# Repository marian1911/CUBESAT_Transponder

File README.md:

Todos los archivos de diseño, simulaciones, componentes y codigo referido a transponder cubesat VHF-UHF

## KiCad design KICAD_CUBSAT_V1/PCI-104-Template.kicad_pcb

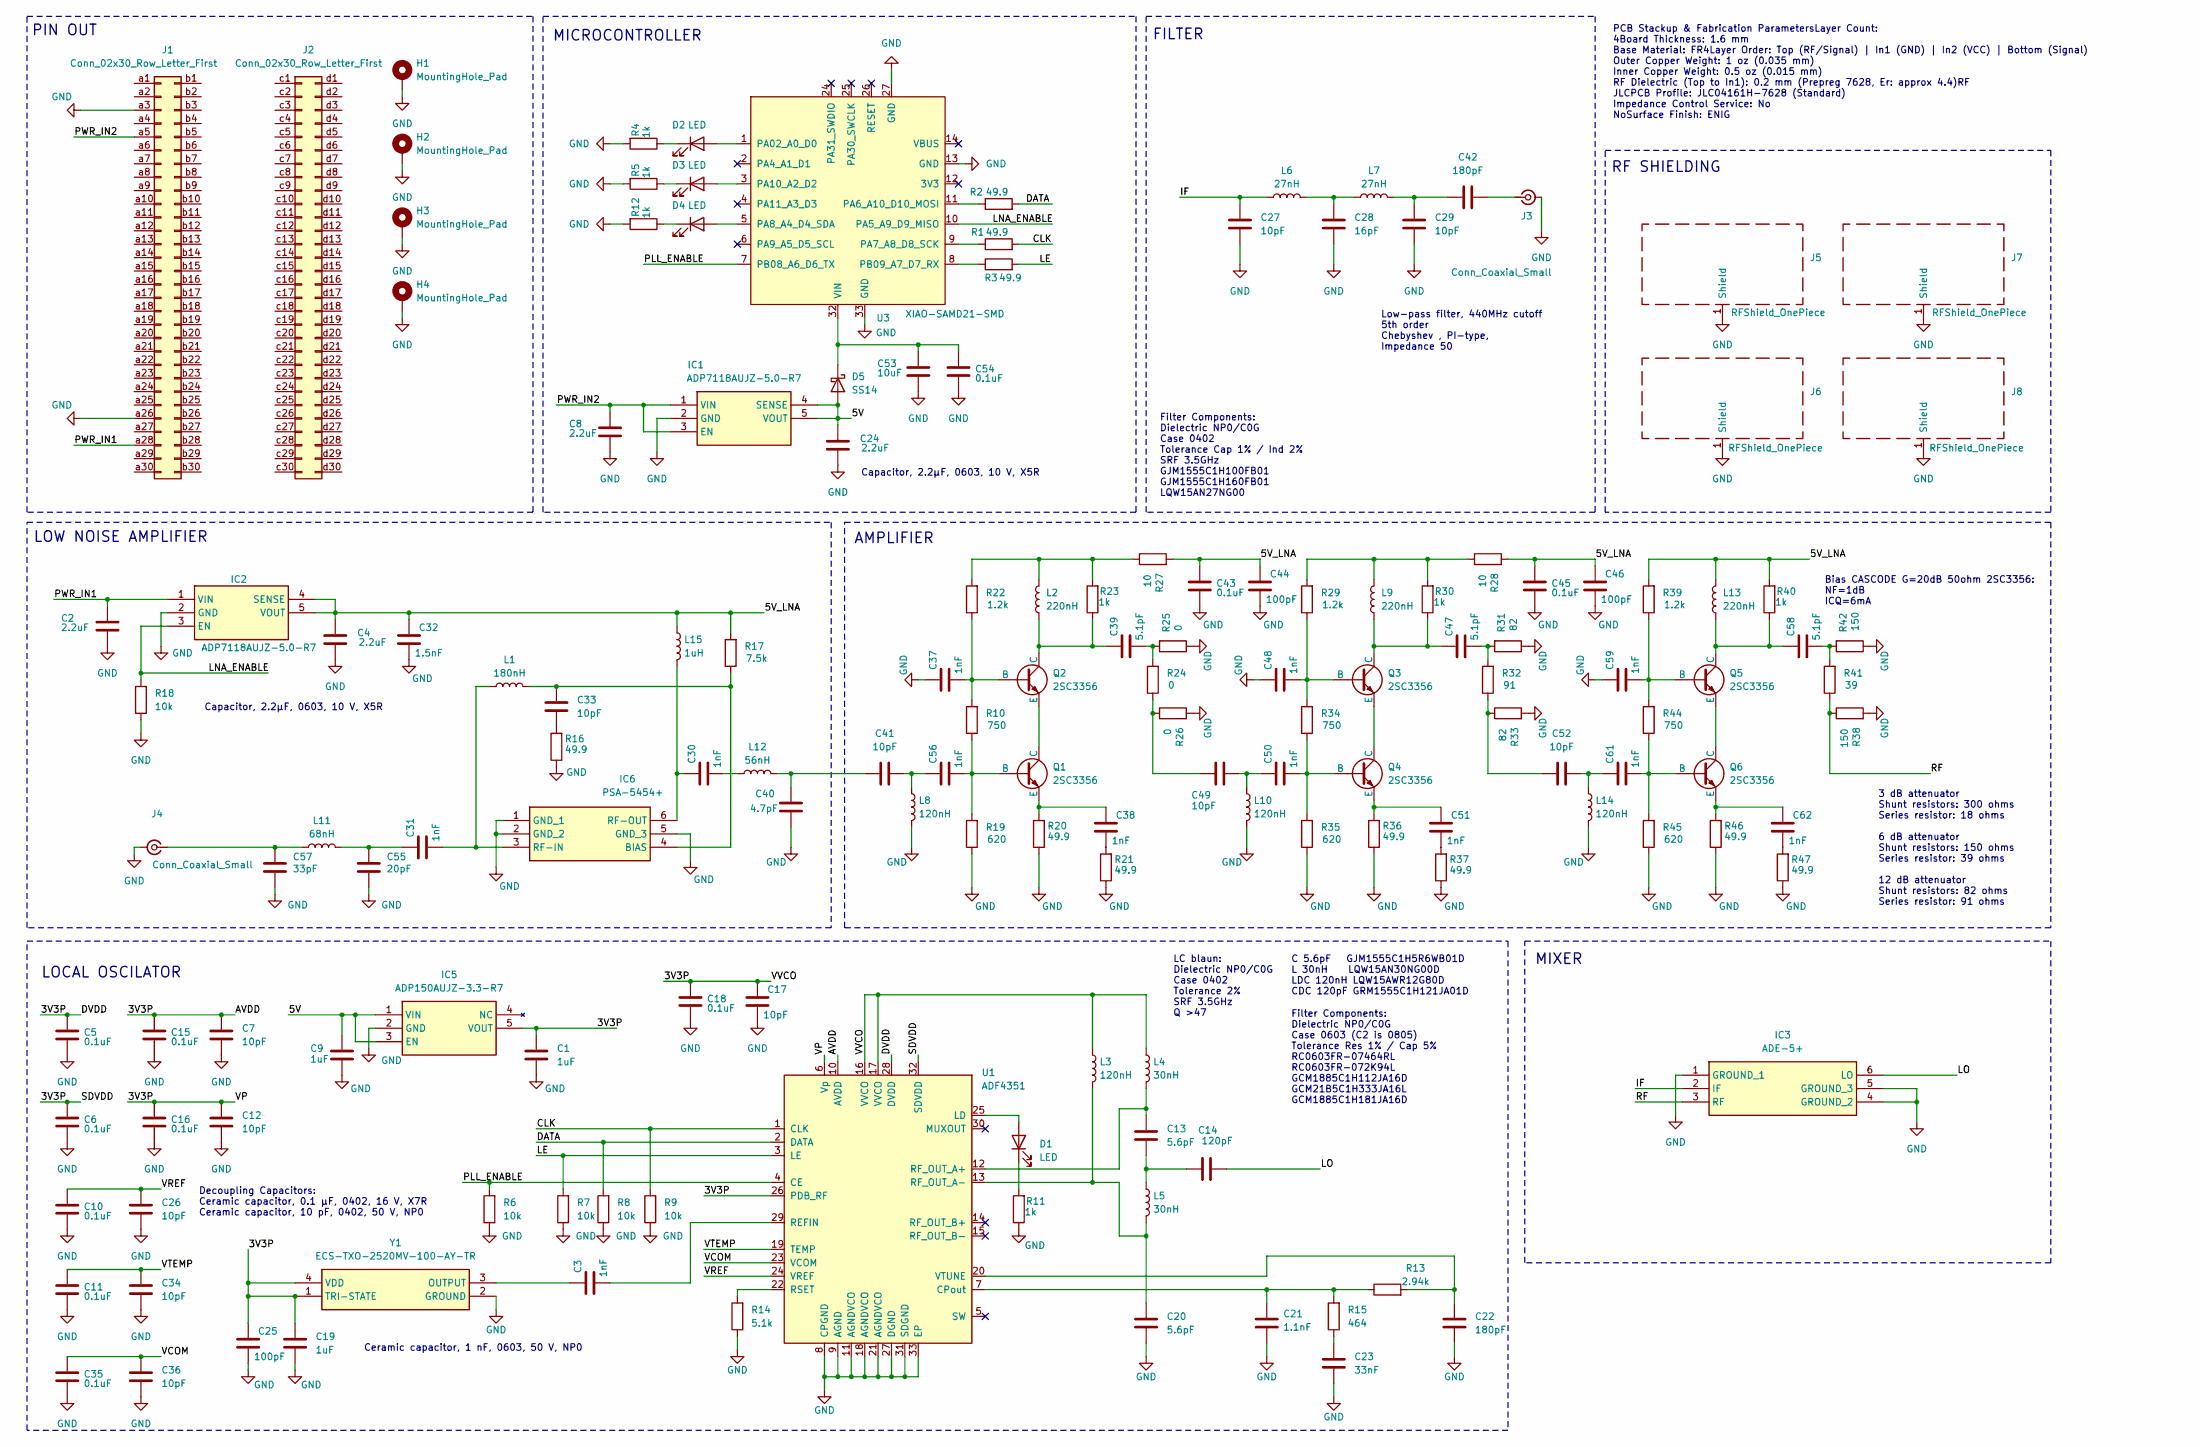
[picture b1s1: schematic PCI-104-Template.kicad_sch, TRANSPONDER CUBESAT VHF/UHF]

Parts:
C1, C9, C19: 1uF; C_0603_1608Metric; Mouser Part Number 81-GRM39R105K10
C2, C4, C8, C24: 2.2uF; C_0603_1608Metric; Mouser Part Number 81-GRM188R61E225KA2D
C3, C30, C31, C37, C38, C48, C50, C51, C56, C59, C61, C62: 1nF; C_0603_1608Metric; Manufacturer_Part_Number GRM1885C1H102JA01D; Mouser Part Number 81-GRM39C102J50
C5, C6, C10, C11, C15, C16, C18, C35, C43, C45, C54: 0.1uF; C_0402_1005Metric; Manufacturer_Part_Number GRM155R71C104KA88D; Mouser Part Number 81-GRM155R71C104KA88
C7, C12, C26, C27, C29, C33, C34, C36, C41, C49, C52: 10pF; C_0402_1005Metric; Manufacturer_Part_Number GJM1555C1H100FB01D; Mouser Part Number 81-GJM1555C1H100FB01
C13, C20: 5.6pF; C_0402_1005Metric; Manufacturer_Part_Number GJM1555C1H5R6WB01D; Mouser Part Number 81-GJM1555C1H5R6WB1D
C14: 120pF; C_0402_1005Metric; Mouser Part Number 81-GRM1555C1H121JA01
C17: 10pF; C_0402_1005Metric; Manufacturer_Part_Number GRM1555C1H100JA01D; Mouser Part Number 81-GRM1555C1H100JA1D
C21: 1.1nF; C_0603_1608Metric; Mouser Part Number 81-GCM1885C1H112JA6D
C22, C42: 180pF; C_0603_1608Metric; Mouser Part Number 81-GCM1885C1H181J16D
C23: 33nF; C_0805_2012Metric; Mouser Part Number 81-GCM21B5C2A333GE2L
C25, C44, C46: 100pF; C_0402_1005Metric; Manufacturer_Part_Number GCM1555C1H101FA16J; Mouser Part Number 81-GCM1555C1H101FA6J
C28: 16pF; C_0402_1005Metric; Manufacturer_Part_Number GJM1555C1H160FB01J; Mouser Part Number 81-GJM1555C1H160FB1J
C32: 1.5nF; C_0603_1608Metric; Manufacturer_Part_Number GRM1885C1H152JA01J; Mouser Part Number 81-GRM185C1H152JA01J
C39, C47, C58: 5.1pF; C_0402_1005Metric; Manufacturer_Part_Number GJM0225C1C5R1BB01L; Mouser Part Number 81-GJM0225C1C5R1BB1L
C40: 4.7pF; C_0402_1005Metric; Manufacturer_Part_Number GJM0225C1E4R7BB01L; Mouser Part Number 81-GJM0225C1E4R7BB1L
C53: 10uF; C_0805_2012Metric; Mouser Part Number 81-GRT21BR61E106KE3L
C55: 20pF; C_0402_1005Metric; Manufacturer_Part_Number GJM1555C1H200FB01D; Mouser Part Number 81-GJM1555C1H200FB1D
C57: 33pF; C_0402_1005Metric; Manufacturer_Part_Number GCM1555C1H330FA16J; Mouser Part Number 81-GCM1555C1H330FA6J
D1, D2, D3, D4: LED; LED_0603_1608Metric; Manufacturer_Part_Number LTST-C190GKT; Mouser Part Number 859-LTST-C190GKT
D5: SS14; D_SMA; Mouser Part Number 512-SS14
H1, H2, H3, H4: MountingHole_Pad; MountingHole_3.2mm_M3_Pad_TopBottom
IC1, IC2: ADP7118AUJZ-5.0-R7; SOT95P280X100-5N; Mouser Part Number 584-P7118WAUJZ-50-R
IC3: ADE-5+; ADE5; Mouser Part Number 139-ADE-5
IC5: ADP150AUJZ-3.3-R7; SOT95P280X100-5N; Mouser Part Number 584-ADP150AUJZ3.3R7
IC6: PSA-5454+; SOT65P215X100-6N; Mouser Part Number 139-PSA-5454
J1, J2: Conn_02x30_Row_Letter_First; PinSocket_2x30_P2.00mm_Vertical
J3, J4: Conn_Coaxial_Small; SMA_Samtec_SMA-J-P-H-ST-EM1_EdgeMount; Manufacturer_Part_Number SMA-J-P-H-ST-EM1; Mouser Part Number 200-SMAJPHSTEM1
J5, J6, J7, J8: RFShield_OnePiece; Laird_Technologies_BMI-S-102_16.50x16.50mm; Manufacturer_Part_Number BMI-S-102; Mouser Part Number 739-BMI-S-102
L1: 180nH; L_0402_1005Metric; Manufacturer_Part_Number LQW15AWR18J80D; Mouser Part Number 81-LQW15AWR18J80D
L2, L9, L13: 220nH; L_0402_1005Metric; Manufacturer_Part_Number LQW18ANR22G00D; Mouser Part Number 81-LQW18ANR22G00D
L3, L8, L10, L14: 120nH; L_0402_1005Metric; Manufacturer_Part_Number LQW15AWR12G80D; Mouser Part Number 81-LQW15AWR12G80D
L4, L5: 30nH; L_0402_1005Metric; Manufacturer_Part_Number LQW15AN30NG00D; Mouser Part Number 81-LQW15AN30NG00D
L6, L7: 27nH; L_0402_1005Metric; Manufacturer_Part_Number LQW15AN27NG00D; Mouser Part Number 81-LQW15AN27NG00D
L11: 68nH; L_0402_1005Metric; Manufacturer_Part_Number LQW15AN68NG0ZD; Mouser Part Number 81-LQW15AN68NG0ZD
L12: 56nH; L_0402_1005Metric; Manufacturer_Part_Number LQW15AN56NG8ZD; Mouser Part Number 81-LQW15AN56NG8ZD
L15: 1uH; L_0805_2012Metric; Manufacturer_Part_Number LQW21FT1R0M0HL; Mouser Part Number 81-LQW21FT1R0M0HL
Q1, Q2, Q3, Q4, Q5, Q6: 2SC3356; SOT-23
R1, R2, R3, R16, R20, R21, R36, R37, R46, R47: 49.9; R_0603_1608Metric; Manufacturer_Part_Number TNPW060349R9FEEA; Mouser Part Number 71-TNPW060349R9FEEA
R4, R5, R11, R12, R23, R30, R40: 1k; R_0603_1608Metric; Mouser Part Number 71-TNPW06031K00FHEA
R6, R7, R8, R9, R18: 10k; R_0603_1608Metric; Mouser Part Number 71-TNPW060310K0FEEA
R10, R34, R44: 750; R_0603_1608Metric; Manufacturer_Part_Number MCT06030D7500BP500; Mouser Part Number 594-MCT06030D7500BP5
R13: 2.94k; R_0603_1608Metric; Manufacturer_Part_Number RC0603FR-072K94L; Mouser Part Number 603-RC0603FR-072K94L
R14: 5.1k; R_0603_1608Metric; Manufacturer_Part_Number TNPW06035K10FHTA; Mouser Part Number 71-TNPW06035K10FHTA
R15: 464; R_0603_1608Metric; Manufacturer_Part_Number RC0603FR-07464RL; Mouser Part Number 603-RC0603FR-07464RL
R17: 7.5k; R_0603_1608Metric; Manufacturer_Part_Number MCT0603MD7501BP500; Mouser Part Number 594-MCT0603MD7501BP5
R19, R35, R45: 620; R_0603_1608Metric; Manufacturer_Part_Number CRCW0201620RFKED; Mouser Part Number 71-CRCW0201620RFKED
R22, R29, R39: 1.2k; R_0603_1608Metric; Manufacturer_Part_Number TNPW02011K20BEED; Mouser Part Number 71-TNPW02011K20BEED
R24, R25, R26: 0; R_0402_1005Metric; Manufacturer_Part_Number CRCW01000000Z0EL; Mouser Part Number 71-CRCW01000000Z0EL
R27, R28: 10; R_0603_1608Metric; Manufacturer_Part_Number MCT06030C1009FP500; Mouser Part Number 594-MCT06030C1009FP5
R31, R33: 82; R_0402_1005Metric; Manufacturer_Part_Number CRCW040282R0FKTD; Mouser Part Number 71-CRCW040282R0FKTD
R32: 91; R_0402_1005Metric; Manufacturer_Part_Number CRCW040291R0FKED; Mouser Part Number 71-CRCW040291R0FKED
R38, R42: 150; R_0402_1005Metric; Manufacturer_Part_Number CRCW0402150RFKED; Mouser Part Number 71-CRCW0402-150-E3
R41: 39; R_0402_1005Metric; Manufacturer_Part_Number CRCW040239R0FKED; Mouser Part Number 71-CRCW040239R0FKED
U1: ADF4351; LFCSP-32-1EP_5x5mm_P0.5mm_EP3.25x3.25mm; Manufacturer_Part_Number ADF4351BCPZ-RL7; Mouser Part Number 584-ADF4351BCPZ-R7
U3: XIAO-SAMD21-SMD; Manufacturer_Part_Number 102010328; Mouser Part Number 713-102010328
Y1: ECS-TXO-2520MV-100-AY-TR; ECSTXO2520MV120AYTR; Mouser Part Number 520-TXO2520MV100AYTR

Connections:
/3V3P: C1.2, C5.2, C6.2, C7.2, C12.2, C15.2, C16.2, C17.2, C18.2, C19.2, C25.2, IC5.5 (VOUT), L3.1, L4.1, U1.6 (Vp), U1.10 (AVDD), U1.16 (VVCO), U1.17 (VVCO), U1.26 (PDB_RF), U1.28 (DVDD), U1.32 (SDVDD), Y1.1 (TRI-STATE), Y1.4 (VDD)
/5V: C9.2, C24.2, D5.2 (A), IC1.4 (SENSE), IC1.5 (VOUT), IC5.1 (VIN), IC5.3 (EN)
/5V_LNA: C4.2, C32.2, C43.2, C44.2, C45.2, C46.2, IC2.4 (SENSE), IC2.5 (VOUT), L13.2, L15.1, R17.2, R27.2, R28.2, R39.2, R40.2
/CLK: R1.2, R9.2, U1.1 (CLK)
/DATA: R2.2, R8.2, U1.2 (DATA)
/IF: C27.2, IC3.2 (IF), L6.1
/LE: R3.2, R7.2, U1.3 (LE)
/LNA_ENABLE: IC2.3 (EN), R18.2, U3.10 (PA5_A9_D9_MISO)
/LO: C14.2, IC3.6 (LO)
/PLL_ENABLE: R6.2, U1.4 (CE), U3.7 (PB08_A6_D6_TX)
/PWR_IN1: C2.2, IC2.1 (VIN), J1.a28
/PWR_IN2: C8.2, IC1.1 (VIN), IC1.3 (EN), J1.a5
/RF: IC3.3 (RF), R38.1, R41.1
/VCOM: C35.2, C36.2, U1.23 (VCOM)
/VREF: C10.2, C26.2, U1.24 (VREF)
/VTEMP: C11.2, C34.2, U1.19 (TEMP)
GND: C1.1, C2.1, C4.1, C5.1, C6.1, C7.1, C8.1, C9.1, C10.1, C11.1, C12.1, C15.1, C16.1, C17.1, C18.1, C19.1, C20.1, C21.1, C22.1, C23.1, C24.1, C25.1, C26.1, C27.1, C28.1, C29.1, C32.1, C34.1, C35.1, C36.1, C37.2, C40.1, C43.1, C44.1, C45.1, C46.1, C48.2, C53.1, C54.1, C55.1, C57.1, C59.2, H1.1, H2.1, H3.1, H4.1, IC1.2 (GND), IC2.2 (GND), IC3.1 (GROUND_1), IC3.4 (GROUND_2), IC3.5 (GROUND_3), IC5.2 (GND), IC6.1 (GND_1), IC6.2 (GND_2), IC6.5 (GND_3), J1.a3, J1.a26, J3.2 (Ext), J4.2 (Ext), J5.1 (Shield), J6.1 (Shield), J7.1 (Shield), J8.1 (Shield), L8.2, L10.2, L14.2, R4.2, R5.2, R6.1, R7.1, R8.1, R9.1, R11.1, R12.2, R14.1, R16.1, R18.1, R19.1, R20.1, R21.1, R25.1, R26.2, R31.1, R33.2, R35.1, R36.1, R37.1, R38.2, R42.1, R45.1, R46.1, R47.1, U1.8 (CPGND), U1.9 (AGND), U1.11 (AGNDVCO), U1.18 (AGNDVCO), U1.21 (AGNDVCO), U1.27 (DGND), U1.31 (SDGND), U1.33 (EP), U3.13 (GND), U3.27 (GND), U3.33 (GND), Y1.2 (GROUND)
unnamed: C13.1, C14.1, L5.1
unnamed: C23.2, R15.1
unnamed: C28.2, L6.2, L7.1
unnamed: C29.2, C42.2, L7.2
unnamed: C30.1, L12.1
unnamed: C31.2, C55.2, L11.2
unnamed: C33.1, R16.2
unnamed: C38.1, R21.2
unnamed: C39.1, R24.2, R25.2
unnamed: C40.2, C41.2, L12.2
unnamed: C41.1, C56.2, L8.1
unnamed: C47.1, R31.2, R32.2
unnamed: C49.1, C50.2, L10.1
unnamed: C49.2, R24.1, R26.1
unnamed: C51.1, R37.2
unnamed: C52.1, C61.2, L14.1
unnamed: C52.2, R32.1, R33.1
unnamed: C58.1, R41.2, R42.2
unnamed: C62.1, R47.2
unnamed: D1.2 (A), U1.25 (LD)
unnamed: D1.1 (K), R11.2
unnamed: D2.2 (A), U3.1 (PA02_A0_D0)
unnamed: D2.1 (K), R4.1
unnamed: D3.2 (A), U3.3 (PA10_A2_D2)
unnamed: D3.1 (K), R5.1
unnamed: D4.2 (A), U3.5 (PA8_A4_D4_SDA)
unnamed: D4.1 (K), R12.1
unnamed: C53.2, C54.2, D5.1 (K), U3.32 (VIN)
unnamed: C33.2, IC6.4 (BIAS), L1.2, R17.1
unnamed: C31.1, IC6.3 (RF-IN), L1.1
unnamed: C30.2, IC6.6 (RF-OUT), L15.2
unnamed: C42.1, J3.1 (In)
unnamed: C57.2, J4.1 (In), L11.1
unnamed: L2.2, R22.2, R23.2, R27.1
unnamed: L9.2, R28.1, R29.2, R30.2
unnamed: C56.1, Q1.2 (B), R10.1, R19.2
unnamed: Q1.1 (C), Q2.3 (E)
unnamed: C38.2, Q1.3 (E), R20.2
unnamed: C37.1, Q2.2 (B), R10.2, R22.1
unnamed: C39.2, L2.1, Q2.1 (C), R23.1
unnamed: C48.1, Q3.2 (B), R29.1, R34.2
unnamed: C47.2, L9.1, Q3.1 (C), R30.1
unnamed: Q3.3 (E), Q4.1 (C)
unnamed: C50.1, Q4.2 (B), R34.1, R35.2
unnamed: C51.2, Q4.3 (E), R36.2
unnamed: C59.1, Q5.2 (B), R39.1, R44.2
unnamed: C58.2, L13.1, Q5.1 (C), R40.1
unnamed: Q5.3 (E), Q6.1 (C)
unnamed: C61.1, Q6.2 (B), R44.1, R45.2
unnamed: C62.2, Q6.3 (E), R46.2
unnamed: C21.2, R13.1, R15.2, U1.7 (CPout)
unnamed: C3.1, U1.29 (REFIN)
unnamed: C13.2, L4.2, U1.12 (RF_OUT_A+)
unnamed: C20.2, L3.2, L5.2, U1.13 (RF_OUT_A-)
unnamed: R14.2, U1.22 (RSET)
unnamed: C22.2, R13.2, U1.20 (VTUNE)
unnamed: R2.1, U3.11 (PA6_A10_D10_MOSI)
unnamed: R1.1, U3.9 (PA7_A8_D8_SCK)
unnamed: R3.1, U3.8 (PB09_A7_D7_RX)
unnamed: C3.2, Y1.3 (OUTPUT)

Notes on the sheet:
Ceramic capacitor, 1 nF, 0603, 50 V, NP0
Filter Components: Dielectric NP0/C0G Case 0402 Tolerance Cap 1% / Ind 2% SRF 3.5GHz GJM1555C1H100FB01 GJM1555C1H160FB01 LQW15AN27NG00
MICROCONTROLLER
Decoupling Capacitors: Ceramic capacitor, 0.1 µF, 0402, 16 V, X7R Ceramic capacitor, 10 pF, 0402, 50 V, NP0
AMPLIFIER
C 5.6pF GJM1555C1H5R6WB01D L 30nH LQW15AN30NG00D LDC 120nH LQW15AWR12G80D CDC 120pF GRM1555C1H121JA01D
MIXER
LC blaun: Dielectric NP0/C0G Case 0402 Tolerance 2% SRF 3.5GHz Q >47
Capacitor, 2.2µF, 0603, 10 V, X5R
FILTER
PCB Stackup & Fabrication ParametersLayer Count: 4Board Thickness: 1.6 mm Base Material: FR4Layer Order: Top (RF/Signal) | In1 (GND) | In2 (VCC) | Bottom (Signal) Outer Copper Weight: 1 oz (0.035 mm) Inner Copper Weight: 0.5 oz (0.015 mm) RF Dielectric (Top to In1): 0.2 mm (Prepreg 7628, Er: approx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
Low-pass filter, 440MHz cutoff 5th order Chebyshev , PI-type, Impedance 50
LOW NOISE AMPLIFIER
RF SHIELDING
LOCAL OSCILATOR
Bias CASCODE G=20dB 50ohm 2SC3356: NF=1dB ICQ=6mA
PIN OUT
3 dB attenuator Shunt resistors: 300 ohms Series resistor: 18 ohms 6 dB attenuator Shunt resistors: 150 ohms Series resistor: 39 ohms 12 dB attenuator Shunt resistors: 82 ohms Series resistor: 91 ohms
Filter Components: Dielectric NP0/C0G Case 0603 (C2 is 0805) Tolerance Res 1% / Cap 5% RC0603FR-07464RL RC0603FR-072K94L GCM1885C1H112JA16D GCM21B5C1H333JA16L GCM1885C1H181JA16D

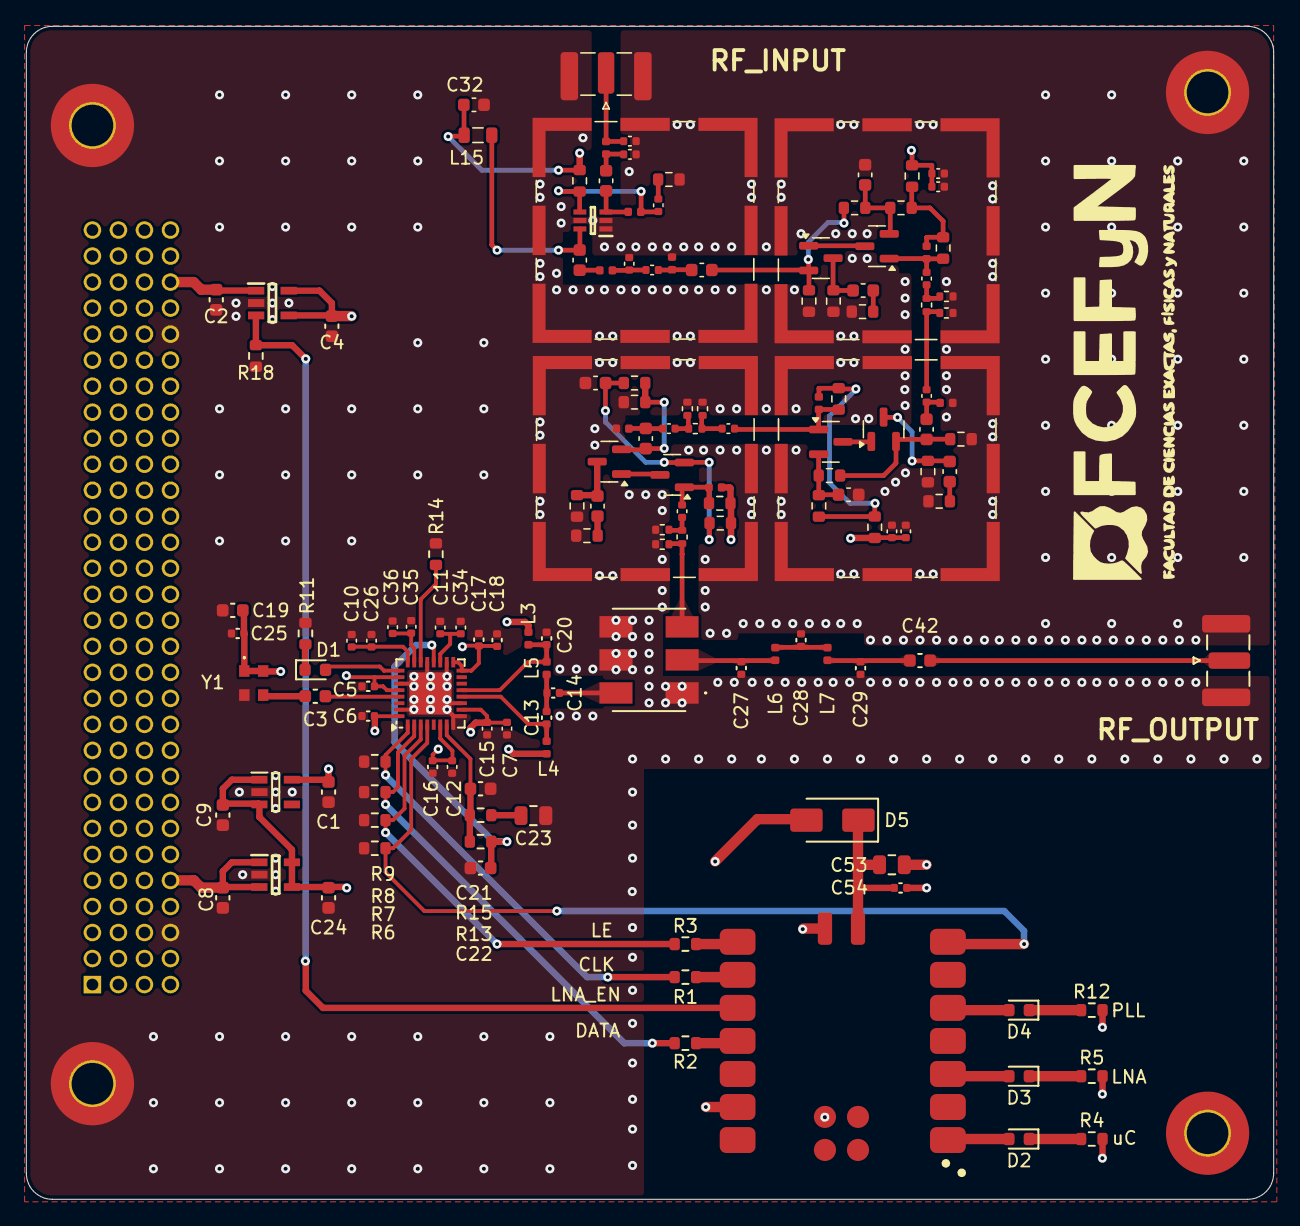
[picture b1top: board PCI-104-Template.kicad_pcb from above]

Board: 4 copper layers, 95.9 x 90.2 mm, 153 parts (0 on the bottom side), 77 nets.
